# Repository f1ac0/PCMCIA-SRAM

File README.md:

# PCMCIA SRAM
This project is a 4MB or 2MB PCMCIA SRAM for Amiga 600 and 1200, using components available in 2020.

Second hand commercial PCMCIA SRAM cards are rare and expensive. Sakura-IT once created new devices, then published their designs when production was discontinued : https://github.com/Sakura-IT/ppa-pcmcia-sram ; thank you. The idea and CPLD CIS code is inspired from it.

About the project :
- It works in A600 and A1200. It is not tested with any other device. It is 16bit only and does not implement 8bit mode that is required to be compliant to the PCMCIA standard.
- It might work as storage, but is not tested. If you need storage you should just use a CF card and adapter anyway. These days nobody would lose their time fitting a battery in a RAM card.
- It is shorter than a regular PCMCIA card, to be more convenient in our Amiga computers. It is thin enough to fit a standard PCMCIA case. You can fit it in the case and connector of a cheap and available PCMCIA CF adapter. 
- It uses components available in 2020. This is important since there have been several designs but many are already obsolete. Reusing the connector of the aforementioned adapter could be important since they are not so common.
- It uses a 5V SRAM chip to get rid of the level converters. These converters take PCB space, have a cost, and need time to solder. The RAM chip is pricey however, so you might chose to make a 2MB card using just one of it.
- The SRAM chip is fast and the CIS advertise the fastest speed possible. Thanks to this the A600 and A1200 runs faster : they benefit from the added RAM with direct access for the CPU, at least for 16bit applications on the A1200. 

About PCMCIA in Amiga computers, you should already know that its address space is sometimes used by internal accelerators and cannot be used at the same time. If you have such an accelerator, you might not be interested to use this project in the same computer anyway. 

# Disclaimer
This is a hobbyist project, it comes with no warranty and no support. Also remember that the Amiga machines are about 30 years old and may fail because of such hardware expansions.

I publish my work under the CC-BY-NC-SA license. The content of this repository is the result of weeks of work, requiring investment in tools, parts, prototypes, and risky tests on his own equipment. For this reason the author does not want third parties to sell products and keep all the profit, usually without even offering support to their customers. If you see people selling this without the consent of the author, don't buy from them.

If you find it useful and want to reward me : I am always looking for Amiga/Amstrad CPC hardware to repair and hack, please contact me.

# BOM
- 1x or 2x CY62167ELL-45ZXI 5V SRAM (do not use 3.3V CY6167EV !) or 1x CY62177ESL--55ZXI 5V SRAM (not tested by me, tell me if this works for you)
- 1x XC9536XL CPLD
- 1x SPX3819M5-L-3-3 3.3v LDO
- 2x 1uF (or more) 0805 capacitors
- 4x or 5x 100nF 0805 capacitors
- 1x female 68pin PCMCIA connector, or a PCMCIA CF adapter from which you will reuse the connector and case

# Making it
I recommend 0.6mm or 0.8mm PCB since it needs to accommodate the PCMCIA connector and height.

Components are SMD, and TSOP RAM have thin pin pitch. You need to know what you are doing.

Check for shorts at least between 5V, 3.3V, and GND traces before applying power !

The programming port does not need to be soldered since it needs to be programmed just once : you can just hold it in place during the few seconds required for programming.

CPLD code is generated using Xilinx ISE 14.7. There are several methods to program the XC9536XL. I personally use xsvfduino : https://github.com/wschutzer/xsvfduino

NOTE : There are solder pads on the PCB that could be used to implement 8/16bit mode and the "high byte on low pins" feature. Cypress replied that the BYTE mode cannot be used dynamically so it might not work. Amiga computers do not and can not use it anyway.

# Case
To reuse a PCMCIA CF adapter case and connector you first need to disassemble the two metal parts from the plastic body.
- The metal parts are identical and held together by hooks every cm on their long sides. Place the adapter vertically with the long side on the bench. Insert a knife blade between the plastic and the metal on the side of the CF opening, cut the glue, and push down to remove the first hook. The hooks on each side are alternated, so after opening the first one on the left you need to open the next from the right, and so on. Do the same on the other log side. The two remaining hooks are on the short side besides the PCMCIA connector, and the metal part is glued to the PCMCIA connector.
- To desolder the connector from the PCB : lift each pin carefully. Use flux.
- Before soldering the PCMCIA connector to your PCB, bend the pins back to their original place so they will make contact to the PCB. Make sure the board and connector are correctly lined up.
- Cut the indent in the plastic body so you can place the board with soldered connector inside. Cut the plastic body 1 or 2 mm longer than the PCB end.
- Ensure that the PCB is installed the correct way in the plastic body : the guides on the plastic body are keyed. The component side is the top side. THIS IS VERY IMPORTANT.
- Test your card before closing the case. Use AmigaTestKit (https://github.com/keirf/Amiga-Stuff/tree/master/testkit) to test the full 4Mb. Once you are sure the board is OK then you are ready to enclose it.
- With strong scissors, cut both metal parts about 1mm shorter than the plastic body. You may damage your scissors however the result is far better than using a saw.
- Be sure that the metal parts are in good shape and the hooks are aligned. Place the lower one in the plastic body.
- Insulate the top one with tape, at least where the capacitors may touch it. Then place it in the plastic body : the hooks will close it.
- The rear end with sharp metal edges require a protection for your fingers. I personally seal it with hot glue.

# Using it
- Plug it to the PCMCIA port
- Turn amiga on

If you care about your Amiga, this might be a bad idea to plug or unplug the device while live. However if you want to access the CIS info using PrepCard, you need to plug the card after powering the computer.

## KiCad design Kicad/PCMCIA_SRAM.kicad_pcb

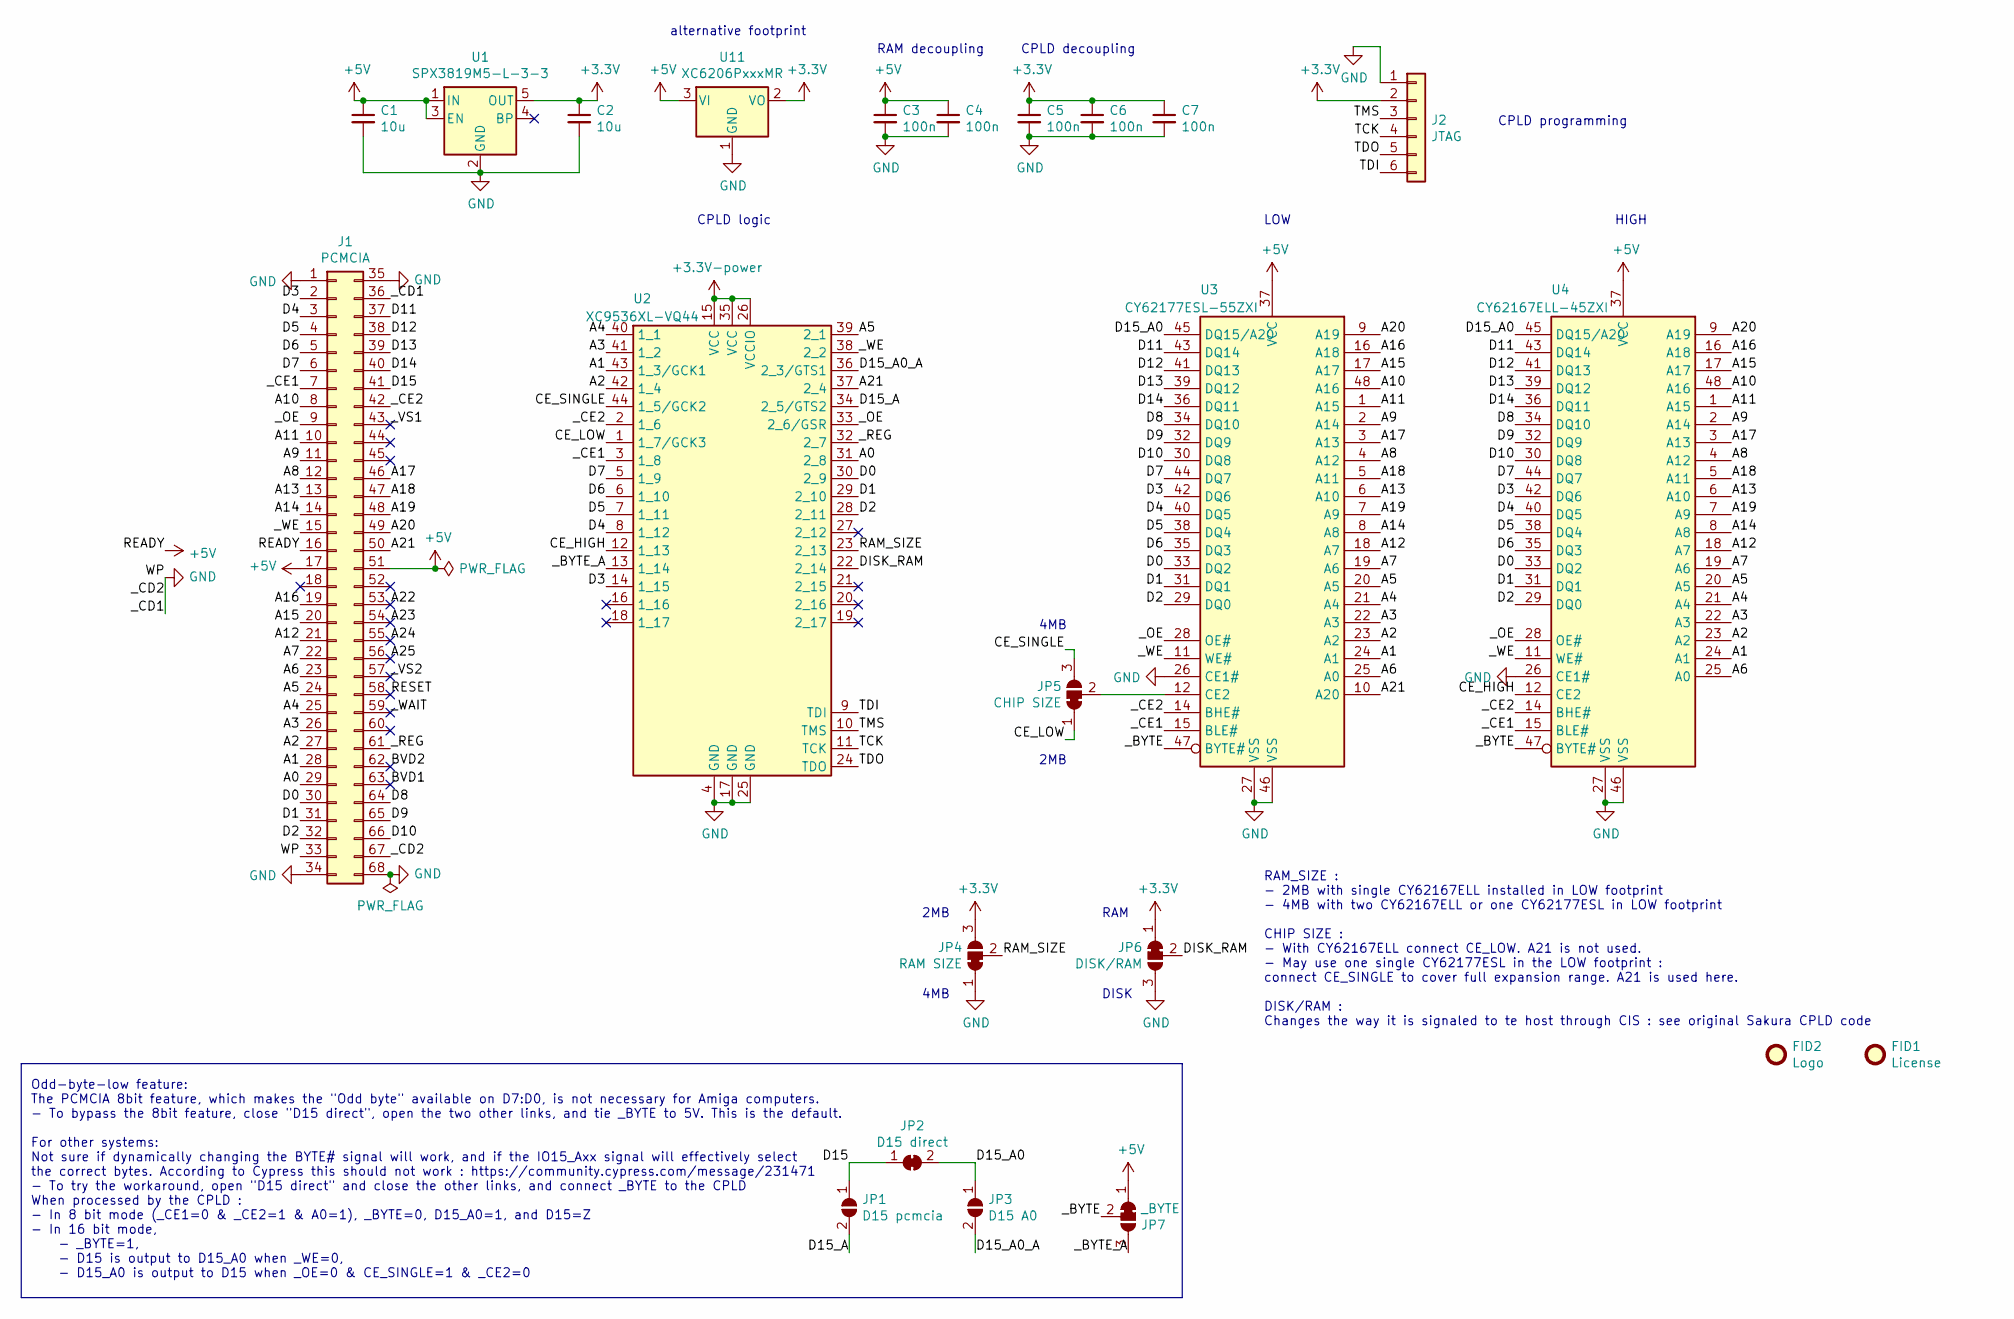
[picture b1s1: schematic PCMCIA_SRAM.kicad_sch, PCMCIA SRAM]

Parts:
C1, C2: 10u; C_0805_2012Metric
C3, C4, C5, C6, C7: 100n; C_0805_2012Metric
FID1: License; CC_BY_NC_SA_square_silkscreen
FID2: Logo; PIC_Cassepanards_GS
J1: PCMCIA; PCMCIA_female_edge_connector
J2: JTAG; PinHeader_1x06_P2.54mm_Vertical
JP1: D15 pcmcia; SolderJumper-2_P1.3mm_Open_RoundedPad1.0x1.5mm
JP2: D15 direct; SolderJumper-2_P1.3mm_Bridged_RoundedPad1.0x1.5mm
JP3: D15 A0; SolderJumper-2_P1.3mm_Open_RoundedPad1.0x1.5mm
JP4: RAM SIZE; SolderJumper-3_P1.3mm_Bridged12_RoundedPad1.0x1.5mm
JP5: CHIP SIZE; SolderJumper-3_P1.3mm_Bridged12_RoundedPad1.0x1.5mm
JP6: DISK/RAM; SolderJumper-3_P1.3mm_Bridged12_RoundedPad1.0x1.5mm
JP7: _BYTE; SolderJumper-3_P1.3mm_Bridged12_RoundedPad1.0x1.5mm
U1: SPX3819M5-L-3-3; SOT-23-5
U2: XC9536XL-VQ44; LQFP-44_10x10mm_P0.8mm
U3: CY62177ESL-55ZXI; TSOP-I-48_18.4x12mm_P0.5mm
U4: CY62167ELL-45ZXI; TSOP-I-48_18.4x12mm_P0.5mm
U11: XC6206PxxxMR; SOT-23

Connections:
+5V: C1.1, C3.1, C4.1, J1.16, J1.17, J1.51, JP7.1 (A), U1.1 (IN), U1.3 (EN), U3.37 (VCC), U4.37 (VCC), U11.3 (VI)
/A0: J1.29, U2.31 (2_8)
/A1: J1.28, U2.43 (1_3/GCK1), U3.24 (A1), U4.24 (A1)
/A2: J1.27, U2.42 (1_4), U3.23 (A2), U4.23 (A2)
/A3: J1.26, U2.41 (1_2), U3.22 (A3), U4.22 (A3)
/A4: J1.25, U2.40 (1_1), U3.21 (A4), U4.21 (A4)
/A5: J1.24, U2.39 (2_1), U3.20 (A5), U4.20 (A5)
/A6: J1.23, U3.25 (A0), U4.25 (A0)
/A7: J1.22, U3.19 (A6), U4.19 (A6)
/A8: J1.12, U3.4 (A12), U4.4 (A12)
/A9: J1.11, U3.2 (A14), U4.2 (A14)
/A10: J1.8, U3.48 (A16), U4.48 (A16)
/A11: J1.10, U3.1 (A15), U4.1 (A15)
/A12: J1.21, U3.18 (A7), U4.18 (A7)
/A13: J1.13, U3.6 (A10), U4.6 (A10)
/A14: J1.14, U3.8 (A8), U4.8 (A8)
/A15: J1.20, U3.17 (A17), U4.17 (A17)
/A16: J1.19, U3.16 (A18), U4.16 (A18)
/A17: J1.46, U3.3 (A13), U4.3 (A13)
/A18: J1.47, U3.5 (A11), U4.5 (A11)
/A19: J1.48, U3.7 (A9), U4.7 (A9)
/A20: J1.49, U3.9 (A19), U4.9 (A19)
/A21: J1.50, U2.37 (2_4), U3.10 (A20)
/A22: J1.53
/A23: J1.54
/A24: J1.55
/A25: J1.56
/BVD1: J1.63
/BVD2: J1.62
/CE_HIGH: U2.12 (1_13), U4.12 (CE2)
/CE_LOW: JP5.1 (A), U2.1 (1_7/GCK3)
/CE_SINGLE: JP5.3 (B), U2.44 (1_5/GCK2)
/D0: J1.30, U2.30 (2_9), U3.33 (DQ2), U4.33 (DQ2)
/D1: J1.31, U2.29 (2_10), U3.31 (DQ1), U4.31 (DQ1)
/D2: J1.32, U2.28 (2_11), U3.29 (DQ0), U4.29 (DQ0)
/D3: J1.2, U2.14 (1_15), U3.42 (DQ6), U4.42 (DQ6)
/D4: J1.3, U2.8 (1_12), U3.40 (DQ5), U4.40 (DQ5)
/D5: J1.4, U2.7 (1_11), U3.38 (DQ4), U4.38 (DQ4)
/D6: J1.5, U2.6 (1_10), U3.35 (DQ3), U4.35 (DQ3)
/D7: J1.6, U2.5 (1_9), U3.44 (DQ7), U4.44 (DQ7)
/D8: J1.64, U3.34 (DQ10), U4.34 (DQ10)
/D9: J1.65, U3.32 (DQ9), U4.32 (DQ9)
/D10: J1.66, U3.30 (DQ8), U4.30 (DQ8)
/D11: J1.37, U3.43 (DQ14), U4.43 (DQ14)
/D12: J1.38, U3.41 (DQ13), U4.41 (DQ13)
/D13: J1.39, U3.39 (DQ12), U4.39 (DQ12)
/D14: J1.40, U3.36 (DQ11), U4.36 (DQ11)
/D15: J1.41, JP1.1 (A), JP2.1 (A)
/D15_A: JP1.2 (B), U2.34 (2_5/GTS2)
/D15_A0: JP2.2 (B), JP3.1 (A), U3.45 (DQ15/A20), U4.45 (DQ15/A20)
/D15_A0_A: JP3.2 (B), U2.36 (2_3/GTS1)
/DISK_RAM: JP6.2 (C), U2.22 (2_14)
/RAM_SIZE: JP4.2 (C), U2.23 (2_13)
/RESET: J1.58
/TCK: J2.4, U2.11 (TCK)
/TDI: J2.6, U2.9 (TDI)
/TDO: J2.5, U2.24 (TDO)
/TMS: J2.3, U2.10 (TMS)
/_BYTE: JP7.2 (C), U3.47 (BYTE#), U4.47 (BYTE#)
/_BYTE_A: JP7.3 (B), U2.13 (1_14)
/_CE1: J1.7, U2.3 (1_8), U3.15 (BLE#), U4.15 (BLE#)
/_CE2: J1.42, U2.2 (1_6), U3.14 (BHE#), U4.14 (BHE#)
/_OE: J1.9, U2.33 (2_6/GSR), U3.28 (OE#), U4.28 (OE#)
/_REG: J1.61, U2.32 (2_7)
/_VS1: J1.43
/_VS2: J1.57
/_WAIT: J1.59
/_WE: J1.15, U2.38 (2_2), U3.11 (WE#), U4.11 (WE#)
GND: C1.2, C2.2, C3.2, C4.2, C5.2, C6.2, C7.2, J1.1, J1.33, J1.34, J1.35, J1.36, J1.67, J1.68, J2.1, JP4.1 (A), JP6.3 (B), U1.2 (GND), U2.4 (GND), U2.17 (GND), U2.25 (GND), U3.26 (CE1#), U3.27 (VSS), U3.46 (VSS), U4.26 (CE1#), U4.27 (VSS), U4.46 (VSS), U11.1 (GND)
unnamed: JP5.2 (C), U3.12 (CE2)

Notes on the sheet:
2MB
4MB
DISK
RAM
HIGH
alternative footprint
CPLD programming
CPLD decoupling
LOW
RAM decoupling
Odd-byte-low feature: The PCMCIA 8bit feature, which makes the "Odd byte" available on D7:D0, is not necessary for Amiga computers. - To bypass the 8bit feature, close "D15 direct", open the two other links, and tie _BYTE to 5V. This is the default. For other systems: Not sure if dynamically changi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
CPLD logic
RAM_SIZE : - 2MB with single CY62167ELL installed in LOW footprint - 4MB with two CY62167ELL or one CY62177ESL in LOW footprint CHIP SIZE : - With CY62167ELL connect CE_LOW. A21 is not used. - May use one single CY62177ESL in the LOW footprint : connect CE_SINGLE to cover full expansion range. A21 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

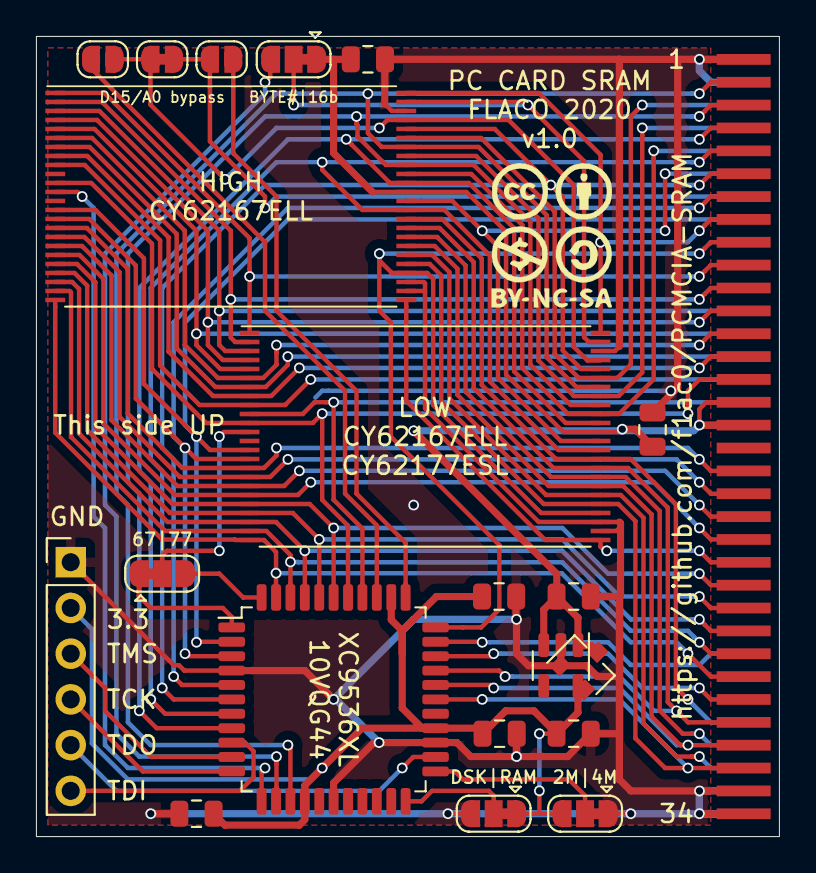
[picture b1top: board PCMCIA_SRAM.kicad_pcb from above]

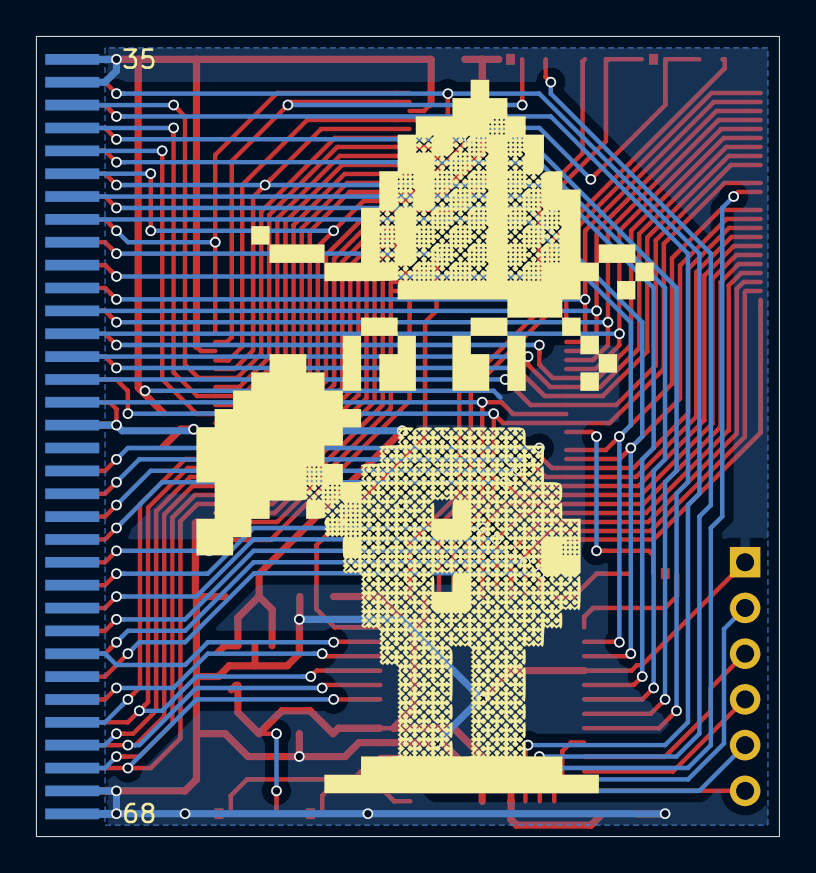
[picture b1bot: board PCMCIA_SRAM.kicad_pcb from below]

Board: 2 copper layers, 41.3 x 44.5 mm, 23 parts (2 on the bottom side), 61 nets.

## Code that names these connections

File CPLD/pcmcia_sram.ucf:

# control signals from PCMCIA
NET "_CE1" LOC = "3";
NET "_CE2" LOC = "2";
NET "_REG" LOC = "32";
NET "_OE" LOC = "33";  # OE from PCMCIA
NET "_WE" LOC = "38";
NET "A0" LOC = "31"; # address bus bit 0
NET "A21" LOC = "37";
NET "D15" LOC = "34";

# switches/jumpers
NET "DISK_RAM" LOC = "22";
NET "RAM_SIZE" LOC = "23";

# control signals to memory
NET "CE_HIGH" LOC = "12";
NET "CE_LOW" LOC = "1";
NET "CE_SINGLE" LOC = "44";
NET "D15_A0" LOC = "36";
NET "_BYTE" LOC = "13";
#NET "oe_even" LOC = "33";
#NET "oe_oddlow" LOC = "29";
#NET "oe_odd" LOC = "28";
#NET "ce_attr_external" LOC = "25";

# address bus (in fact A1-A5)
NET "A<1>" LOC = "43";
NET "A<2>" LOC = "42";
NET "A<3>" LOC = "41";
NET "A<4>" LOC = "40";
NET "A<5>" LOC = "39";

# lowest 8 bits of data bus
NET "D<0>" LOC = "30";
NET "D<1>" LOC = "29";
NET "D<2>" LOC = "28";
NET "D<3>" LOC = "14";
NET "D<4>" LOC = "8";
NET "D<5>" LOC = "7";
NET "D<6>" LOC = "6";
NET "D<7>" LOC = "5";

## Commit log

2020-08-13 Respository init with v0.1 KiCAD files, Readme and License
2020-08-13 v1.0 KiCAD files, D15/A0 bypass by default
2020-08-13 Readme typos
2021-01-18 Made pads shorter on PCMCIA connector. Corrected license to CC-BY-NC-SA.
2022-10-13 Kicad: conversion to Kicad 6 ; repo URL on PCB silkscreen.
2022-10-13 Public repository init with schematic, Gerbers, ibom, CPLD xsvf, Photo, Readme, License
2024-05-09 Add photos of the assembly process
2024-12-27 CPLD: added a version with no attribute ROM to test with LeCroy scope ; please report if it is working for you

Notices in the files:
Kicad/PCMCIA_SRAM.kicad_pcb:
FLACO 2019 - Creative Commons Attribution-ShareAlike 4.0 license
